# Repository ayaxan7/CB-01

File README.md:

# NeonCore

## RP2040 Cyberpunk Development Badge

NeonCore is a cyberpunk-inspired electronic badge built around the RP2040 microcontroller. The project combines embedded hardware with custom PCB artwork, resulting in a compact development badge that is both functional and visually distinctive.

Designed entirely in KiCad, the board includes USB Type-C connectivity, Li-Po battery support with onboard charging, RGB lighting, OLED display support, external QSPI flash memory, and onboard power management. The goal was to create a portable embedded platform that could later be extended with custom firmware and interactive applications.

---

## Features

- RP2040 Dual-Core Microcontroller
- USB Type-C Connectivity
- 3.7V Li-Po Battery Support
- MCP73831 Battery Charging Circuit
- ME6211 3.3V Voltage Regulator
- 16 × SK6812 Mini RGB LEDs
- 1.3" OLED Display Support
- External QSPI Flash Memory
- Onboard Power Switch
- Custom Cyberpunk PCB Artwork

---
## Project Status

- Schematic Completed
- PCB Layout Completed
- Design Rule Check (DRC) Passed
- Gerber Files Generated
- Ready for Fabrication

---

## Tools Used

- KiCad
- Git
- GitHub

---

<p align="center">
Designed and developed using KiCad.
</p>

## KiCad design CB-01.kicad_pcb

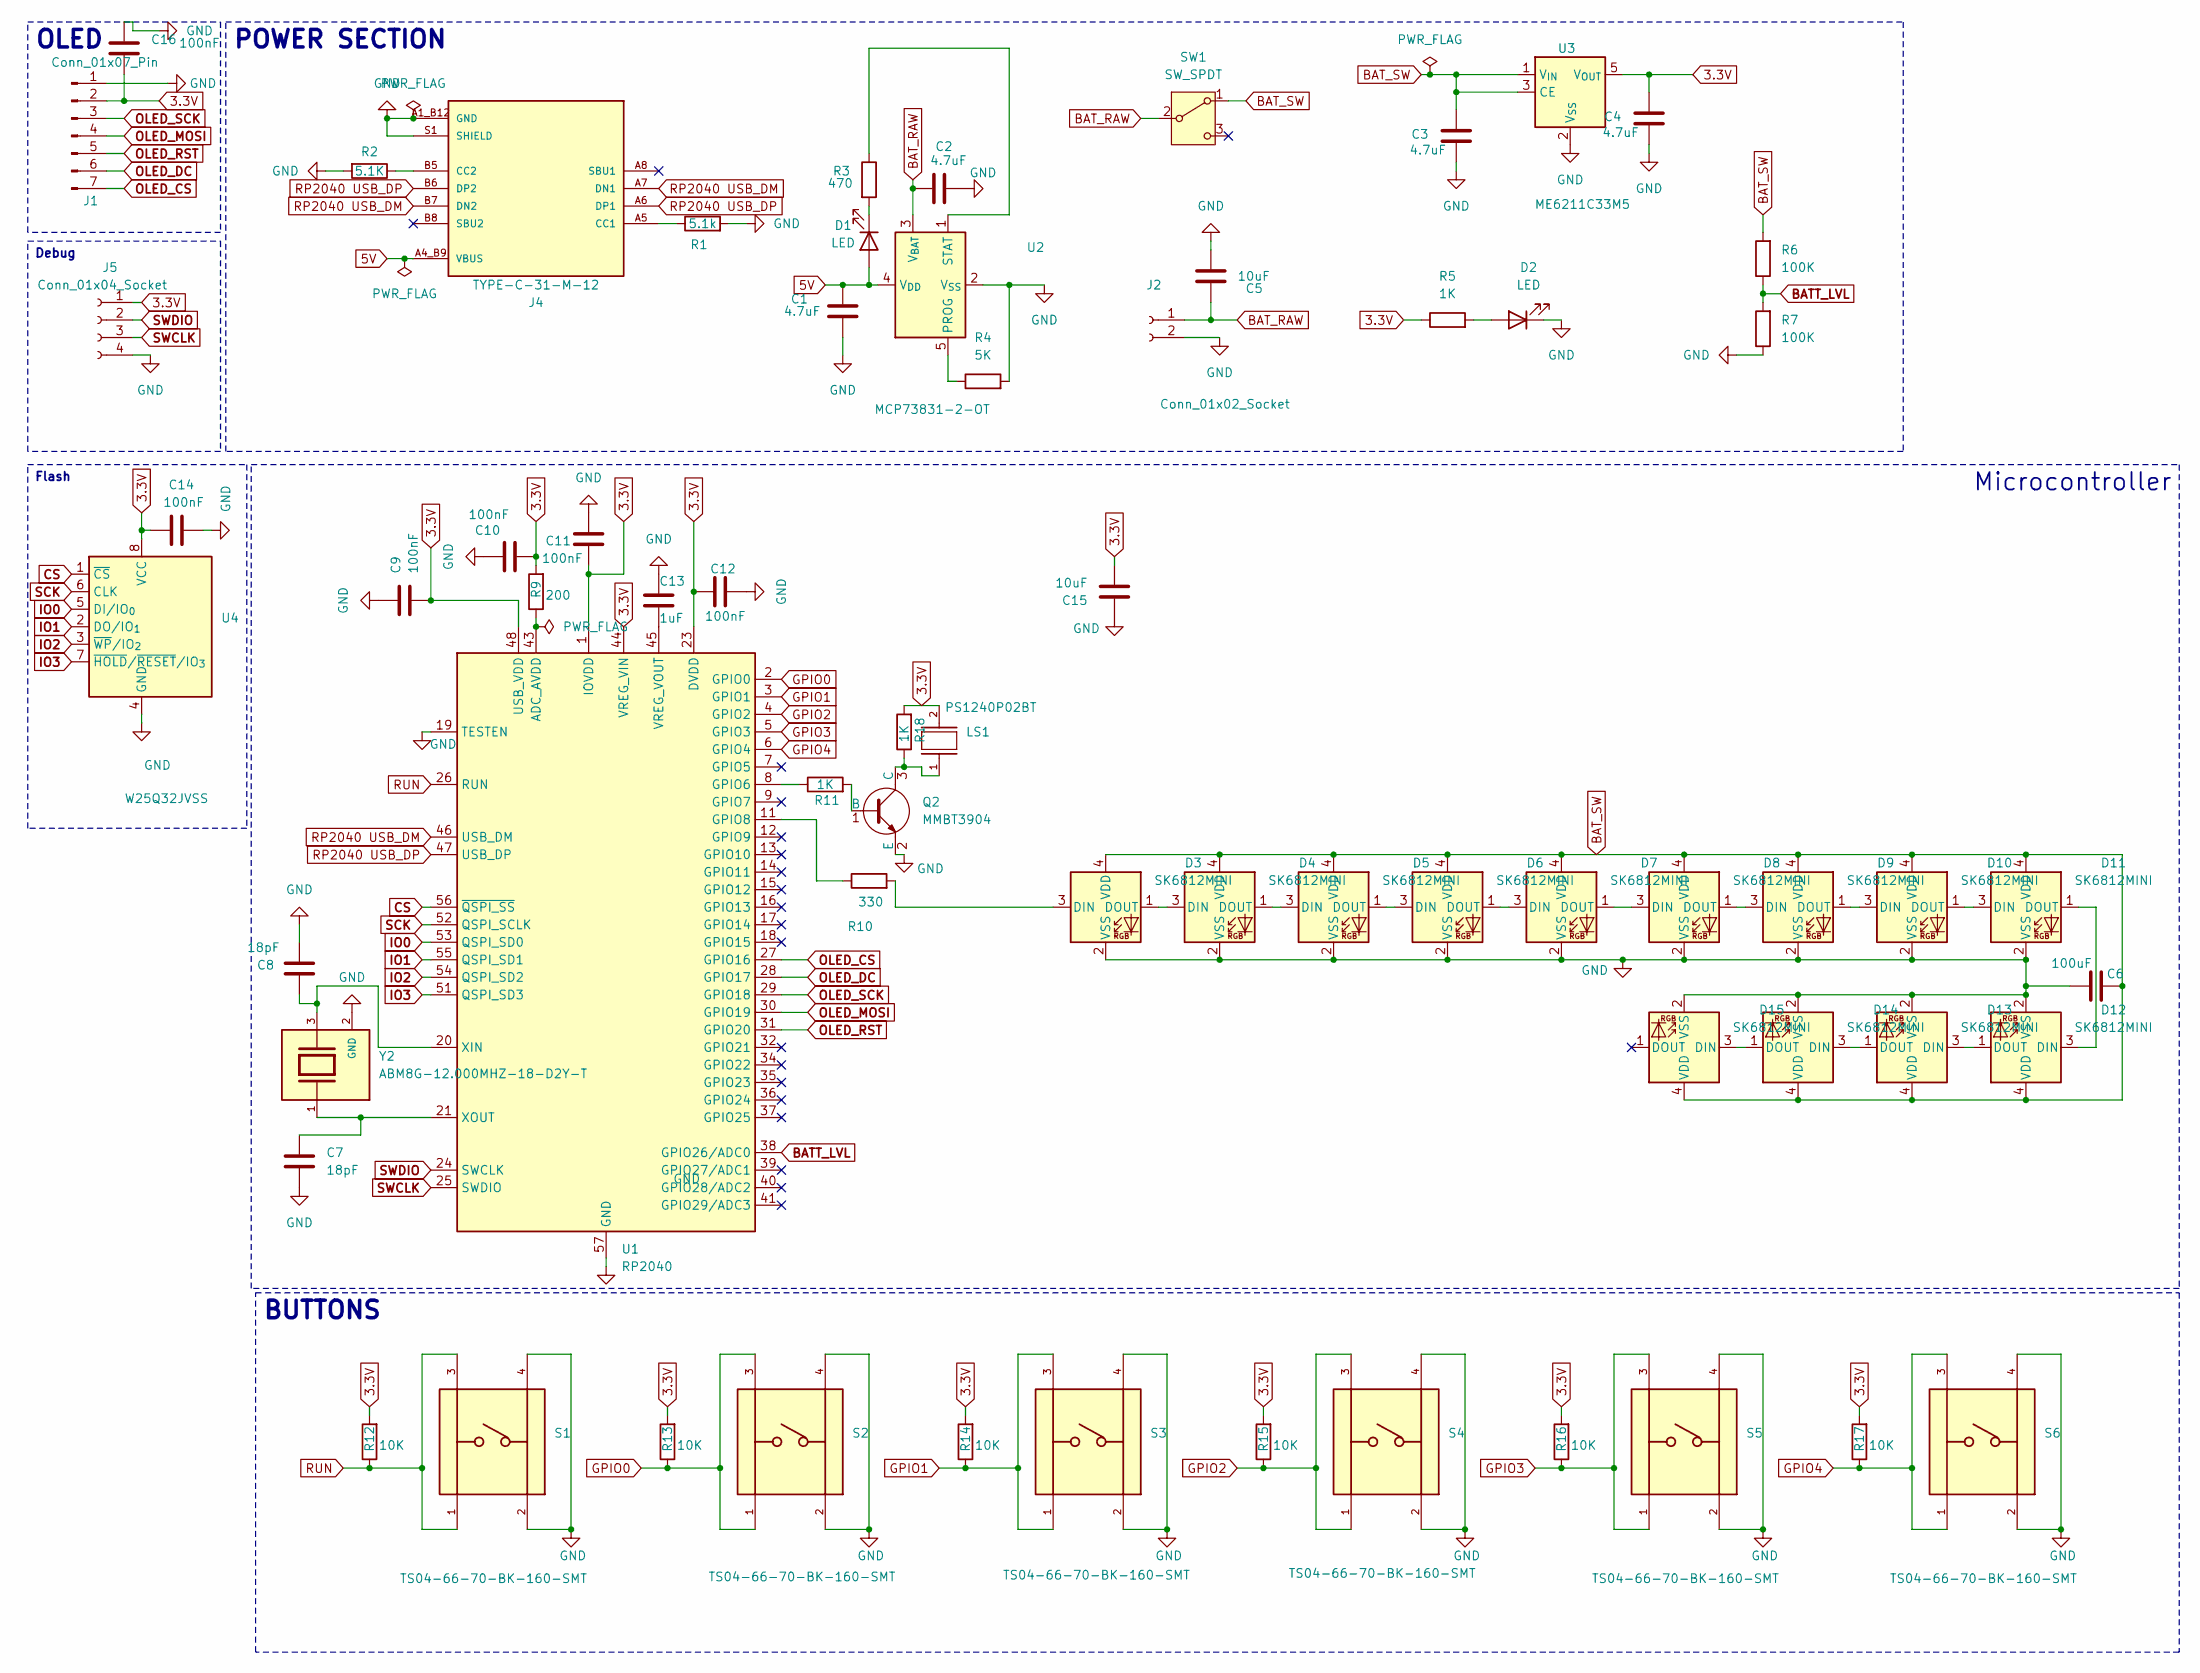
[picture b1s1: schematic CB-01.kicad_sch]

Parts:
C1, C2, C3, C4: 4.7uF; C_0805_2012Metric; MANUFACTURER PART NUMBER CL21A475KAQNNNE
C5, C15: 10uF; C_0805_2012Metric; MANUFACTURER PART NUMBER CL21A106KQFNNNE
C6: 100uF; C_0805_2012Metric; MANUFACTURER PART NUMBER GRM21BR60G107ME11K
C7, C8: 18pF; C_0805_2012Metric; MANUFACTURER PART NUMBER CC0805JRNPO9BN180
C9, C10, C11, C12, C14, C16: 100nF; C_0805_2012Metric; MANUFACTURER PART NUMBER CL21B104KBCNNNC
C13: 1uF; C_0805_2012Metric; MANUFACTURER PART NUMBER CL21B105KAFNNNE
D1, D2: LED; LED_0805_2012Metric; MANUFACTURER PART NUMBER LTST-C171KGKT
D3, D4, D5, D6, D7, D8, D9, D10, D11, D12, D13, D14, D15: SK6812MINI; LED_SK6812MINI_PLCC4_3.5x3.5mm_P1.75mm; MANUFACTURER PART NUMBER 2659
J1: Conn_01x07_Pin; PinHeader_1x07_P2.54mm_Vertical; MANUFACTURER PART NUMBER 61300711121
J2: Conn_01x02_Socket; JST_S2B-PH-K-S_LF__SN_; MANUFACTURER PART NUMBER S2B-PH-K-S
J4: TYPE-C-31-M-12; HRO_TYPE-C-31-M-12; PARTREV 2020.12.08
J5: Conn_01x04_Socket; PinHeader_1x04_P2.54mm_Vertical; MANUFACTURER PART NUMBER 61300411121
LS1: PS1240P02BT; XDCR_PS1240P02BT; MANUFACTURER PART NUMBER PS1240P02BT
Q2: MMBT3904; P200_SOT-23
R1: 5.1k; R_0805_2012Metric; MANUFACTURER PART NUMBER RC0805JR-075K1L
R2: 5.1K; R_0805_2012Metric; MANUFACTURER PART NUMBER RC0805JR-075K1L
R3: 470; R_0805_2012Metric; MANUFACTURER PART NUMBER CRGCQ0805J470R
R4: 5K; R_0805_2012Metric; MANUFACTURER PART NUMBER CRT0805-BY-5001EAS
R5, R11, R18: 1K; R_0805_2012Metric; MANUFACTURER PART NUMBER RES 1K OHM 1% 1/8W 0805
R6, R7: 100K; R_0805_2012Metric; MANUFACTURER PART NUMBER RC0805FR-07100KL
R9: 200; R_0805_2012Metric; MANUFACTURER PART NUMBER CRCW0805200RFKEA
R10: 330; R_0805_2012Metric; MANUFACTURER PART NUMBER RC0805FR-07330RL
R12, R13, R14, R15, R16, R17: 10K; R_0805_2012Metric; MANUFACTURER PART NUMBER RC0805FR-0710KL
S1, S2, S3, S4, S5, S6: TS04-66-70-BK-160-SMT; SW_TS04-66-70-BK-160-SMT; PARTREV 1.0
SW1: SW_SPDT; SW_JS102011SAQN; MANUFACTURER PART NUMBER JS102011SAQN
U1: RP2040; QFN-56-1EP_7x7mm_P0.4mm_EP3.2x3.2mm; MANUFACTURER PART NUMBER RP2040
U2: MCP73831-2-OT; SOT-23-5; MANUFACTURER PART NUMBER MCP73831T-2ACI/OT
U3: ME6211C33M5; SOT-23-5; MANUFACTURER PART NUMBER ME6211C33M5G-N
U4: W25Q32JVSS; SOIC-8_5.3x5.3mm_P1.27mm; MANUFACTURER PART NUMBER W25Q32JVSSIM
Y2: ABM8G-12.000MHZ-18-D2Y-T; XTAL_ABM8G-12.000MHZ-18-D2Y-T; PARTREV 08.13.15

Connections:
3.3V: C4.1, C9.2, C10.2, C11.2, C12.2, C14.2, C15.2, C16.2, J1.2, J5.1, LS1.2, R5.1, R9.2, R12.2, R13.2, R14.2, R15.2, R16.2, R17.2, R18.2, U1.1 (IOVDD), U1.10 (IOVDD), U1.22 (IOVDD), U1.23 (DVDD), U1.33 (IOVDD), U1.42 (IOVDD), U1.44 (VREG_VIN), U1.48 (USB_VDD), U1.49 (IOVDD), U1.50 (DVDD), U3.5 (V_{OUT}), U4.8 (VCC)
5V: C1.1, D1.2 (A), J4.A4_B9 (VBUS), J4.B4_A9 (VBUS), U2.4 (V_{DD})
BATT_LVL: R6.1, R7.2, U1.38 (GPIO26/ADC0)
BAT_RAW: C2.1, C5.1, J2.1, SW1.2 (B), U2.3 (V_{BAT})
BAT_SW: C3.1, C6.2, D3.4 (VDD), D4.4 (VDD), D5.4 (VDD), D6.4 (VDD), D7.4 (VDD), D8.4 (VDD), D9.4 (VDD), D10.4 (VDD), D11.4 (VDD), D12.4 (VDD), D13.4 (VDD), D14.4 (VDD), D15.4 (VDD), R6.2, SW1.1 (A), U3.1 (V_{IN}), U3.3 (CE)
CS: U1.56 (~QSPI_SS), U4.1 (~CS)
GND: C1.2, C2.2, C3.2, C4.2, C5.2, C6.1, C7.2, C8.2, C9.1, C10.1, C11.1, C12.1, C13.1, C14.1, C15.1, C16.1, D2.1 (K), D3.2 (VSS), D4.2 (VSS), D5.2 (VSS), D6.2 (VSS), D7.2 (VSS), D8.2 (VSS), D9.2 (VSS), D10.2 (VSS), D11.2 (VSS), D12.2 (VSS), D13.2 (VSS), D14.2 (VSS), D15.2 (VSS), J1.1, J2.2, J4.A1_B12 (GND), J4.B1_A12 (GND), J4.S1 (SHIELD), J4.S2 (SHIELD), J4.S3 (SHIELD), J4.S4 (SHIELD), J5.4, Q2.2 (E), R1.2, R2.2, R4.2, R7.1, S1.2, S1.4, S2.2, S2.4, S3.2, S3.4, S4.2, S4.4, S5.2, S5.4, S6.2, S6.4, U1.19 (TESTEN), U1.57 (GND), U2.2 (V_{SS}), U3.2 (V_{SS}), U4.4 (GND), Y2.2 (GND), Y2.4 (GND)
GPIO0: R13.1, S2.1, S2.3, U1.2 (GPIO0)
GPIO1: R14.1, S3.1, S3.3, U1.3 (GPIO1)
GPIO2: R15.1, S4.1, S4.3, U1.4 (GPIO2)
GPIO3: R16.1, S5.1, S5.3, U1.5 (GPIO3)
GPIO4: R17.1, S6.1, S6.3, U1.6 (GPIO4)
IO0: U1.53 (QSPI_SD0), U4.5 (DI/IO_{0})
IO1: U1.55 (QSPI_SD1), U4.2 (DO/IO_{1})
IO2: U1.54 (QSPI_SD2), U4.3 (~WP/IO_{2})
IO3: U1.51 (QSPI_SD3), U4.7 (~HOLD/~RESET/IO_{3})
unnamed: D1.1 (K), R3.2
unnamed: D2.2 (A), R5.2
unnamed: D3.3 (DIN), R10.2
unnamed: D3.1 (DOUT), D4.3 (DIN)
unnamed: D4.1 (DOUT), D5.3 (DIN)
unnamed: D5.1 (DOUT), D6.3 (DIN)
unnamed: D6.1 (DOUT), D7.3 (DIN)
unnamed: D7.1 (DOUT), D8.3 (DIN)
unnamed: D8.1 (DOUT), D9.3 (DIN)
unnamed: D9.1 (DOUT), D10.3 (DIN)
unnamed: D10.1 (DOUT), D11.3 (DIN)
unnamed: D11.1 (DOUT), D12.3 (DIN)
unnamed: D12.1 (DOUT), D13.3 (DIN)
unnamed: D13.1 (DOUT), D14.3 (DIN)
unnamed: D14.1 (DOUT), D15.3 (DIN)
unnamed: J4.A5 (CC1), R1.1
unnamed: J4.B5 (CC2), R2.1
unnamed: Q2.1 (B), R11.2
unnamed: LS1.1, Q2.3 (C), R18.1
unnamed: R9.1, U1.43 (ADC_AVDD)
unnamed: R11.1, U1.8 (GPIO6)
unnamed: R10.1, U1.11 (GPIO8)
unnamed: C13.2, U1.45 (VREG_VOUT)
unnamed: C8.1, U1.20 (XIN), Y2.3
unnamed: C7.1, U1.21 (XOUT), Y2.1
unnamed: R4.1, U2.5 (PROG)
unnamed: R3.1, U2.1 (STAT)
OLED_CS: J1.7, U1.27 (GPIO16)
OLED_DC: J1.6, U1.28 (GPIO17)
OLED_MOSI: J1.4, U1.30 (GPIO19)
OLED_RST: J1.5, U1.31 (GPIO20)
OLED_SCK: J1.3, U1.29 (GPIO18)
RP2040 USB_DM: J4.A7 (DN1), J4.B7 (DN2), U1.46 (USB_DM)
RP2040 USB_DP: J4.A6 (DP1), J4.B6 (DP2), U1.47 (USB_DP)
RUN: R12.1, S1.1, S1.3, U1.26 (RUN)
SCK: U1.52 (QSPI_SCLK), U4.6 (CLK)
SWCLK: J5.3, U1.25 (SWDIO)
SWDIO: J5.2, U1.24 (SWCLK)

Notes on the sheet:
BUTTONS
Flash
Microcontroller
Debug
OLED
POWER SECTION

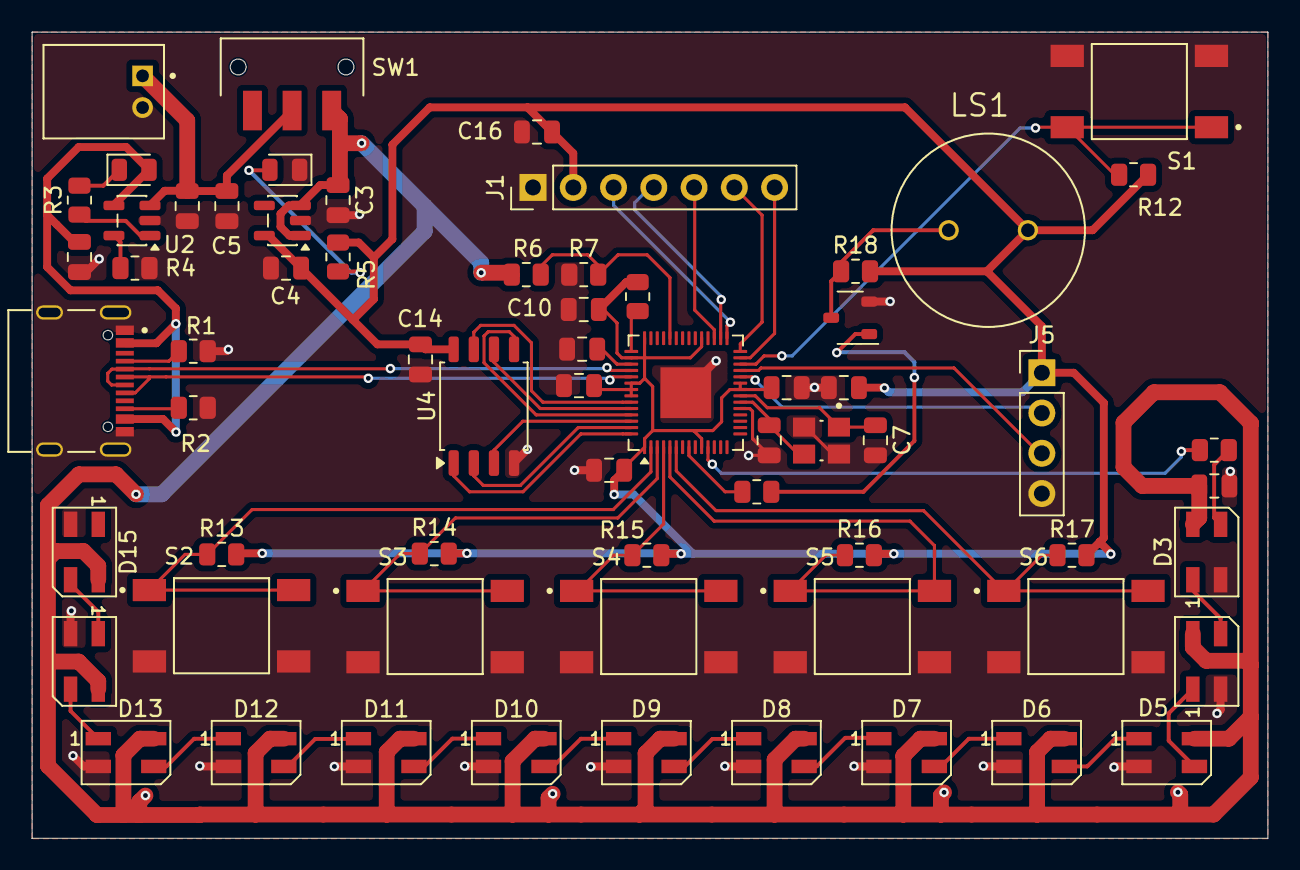
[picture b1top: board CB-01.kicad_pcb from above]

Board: 4 copper layers, 78.0 x 50.9 mm, 66 parts (0 on the bottom side), 54 nets.

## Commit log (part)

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2026-06-24 first kick
2026-06-24 updated files
